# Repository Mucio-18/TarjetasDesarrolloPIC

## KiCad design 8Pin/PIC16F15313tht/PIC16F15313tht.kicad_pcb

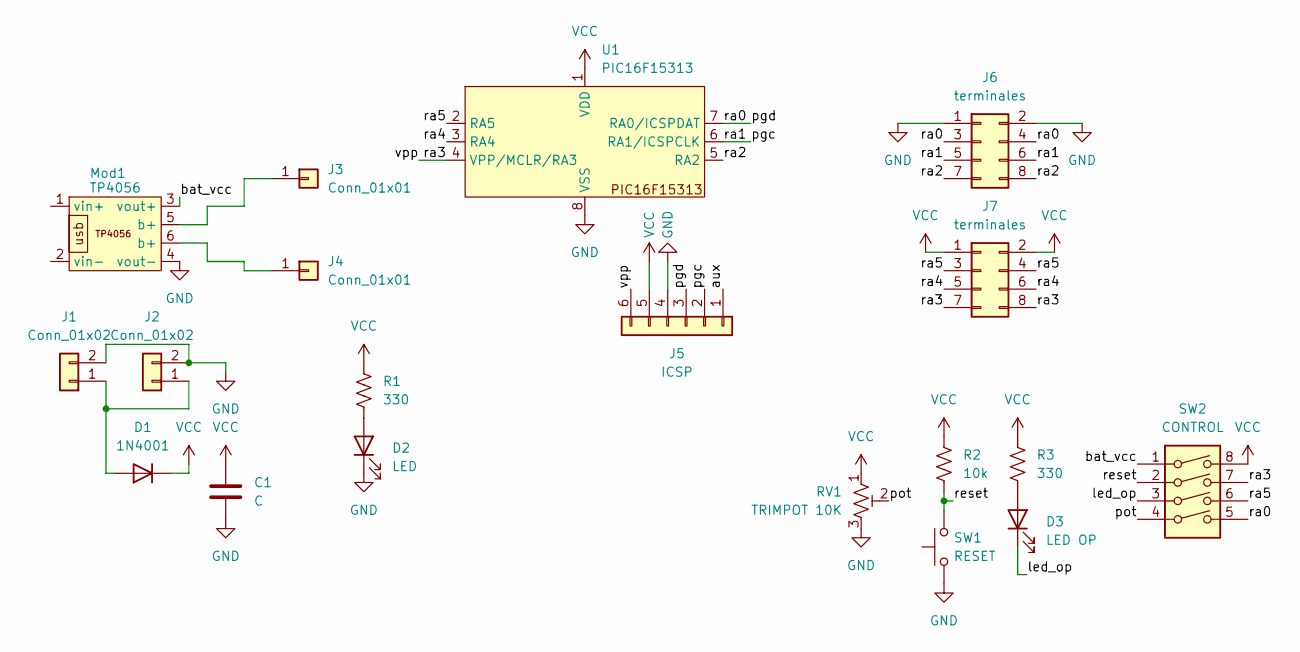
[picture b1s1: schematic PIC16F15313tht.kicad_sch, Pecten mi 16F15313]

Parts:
C1: C; C_Disc_D5.0mm_W2.5mm_P5.00mm
D1: 1N4001; D_DO-41_SOD81_P10.16mm_Horizontal
D2: LED; LED_D3.0mm
D3: LED OP; LED_D3.0mm
J1, J2: Conn_01x02; PinHeader_1x02_P2.54mm_Vertical
J3, J4: Conn_01x01; TestPoint_Pad_D2.5mm
J5: ICSP; PinHeader_1x06_P2.54mm_Horizontal
J6, J7: terminales; PinHeader_2x04_P2.54mm_Vertical
Mod1: TP4056
R1, R3: 330; R_Axial_DIN0207_L6.3mm_D2.5mm_P7.62mm_Horizontal
R2: 10k; R_Axial_DIN0207_L6.3mm_D2.5mm_P7.62mm_Horizontal
RV1: TRIMPOT 10K; Potentiometer_Bourns_3296W_Vertical
SW1: RESET; SW_PUSH_6mm
SW2: CONTROL; SW_DIP_SPSTx04_Slide_6.7x11.72mm_W7.62mm_P2.54mm_LowProfile
U1: PIC16F15313; DIP-8_W7.62mm

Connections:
/aux: J5.1
/bat_vcc: Mod1.3 (vout+), SW2.1
/led_op: D3.1 (K), SW2.3
/pgc: J5.2, J6.5, J6.6, U1.6 (RA1/ICSPCLK)
/pgd: J5.3, J6.3, J6.4, SW2.5, U1.7 (RA0/ICSPDAT)
/pot: RV1.2, SW2.4
/ra2: J6.7, J6.8, U1.5 (RA2)
/ra3: J5.6, J7.7, J7.8, SW2.7, U1.4 (VPP/MCLR/RA3)
/ra4: J7.5, J7.6, U1.3 (RA4)
/ra5: J7.3, J7.4, SW2.6, U1.2 (RA5)
/reset: R2.2, SW1.2, SW2.2
GND: C1.2, D2.1 (K), J1.2, J2.2, J5.4, J6.1, J6.2, Mod1.4 (vout-), RV1.3, SW1.1, U1.8 (VSS)
unnamed: D1.2 (A), J1.1, J2.1
unnamed: D2.2 (A), R1.2
unnamed: D3.2 (A), R3.2
unnamed: J3.1, Mod1.5 (b+)
unnamed: J4.1, Mod1.6 (b+)
VCC: C1.1, D1.1 (K), J5.5, J7.1, J7.2, R1.1, R2.1, R3.1, RV1.1, SW2.8, U1.1 (VDD)

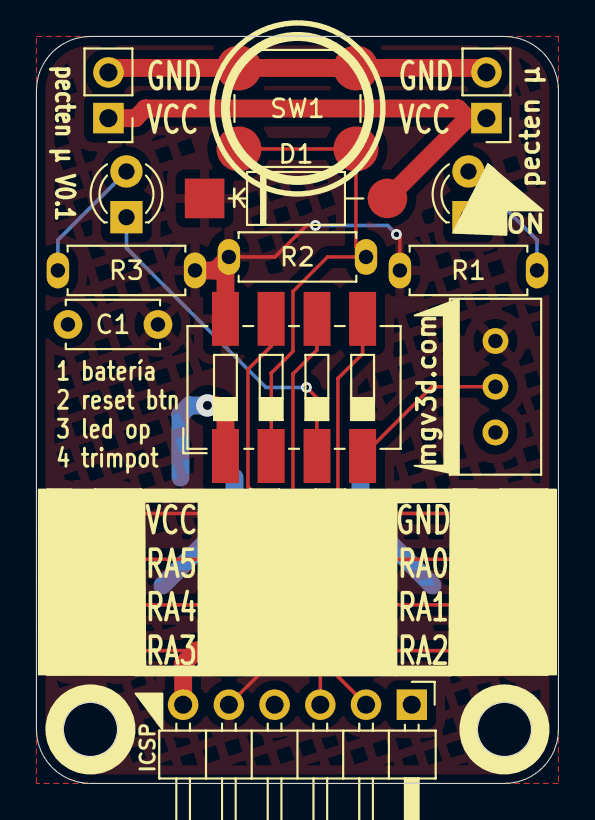
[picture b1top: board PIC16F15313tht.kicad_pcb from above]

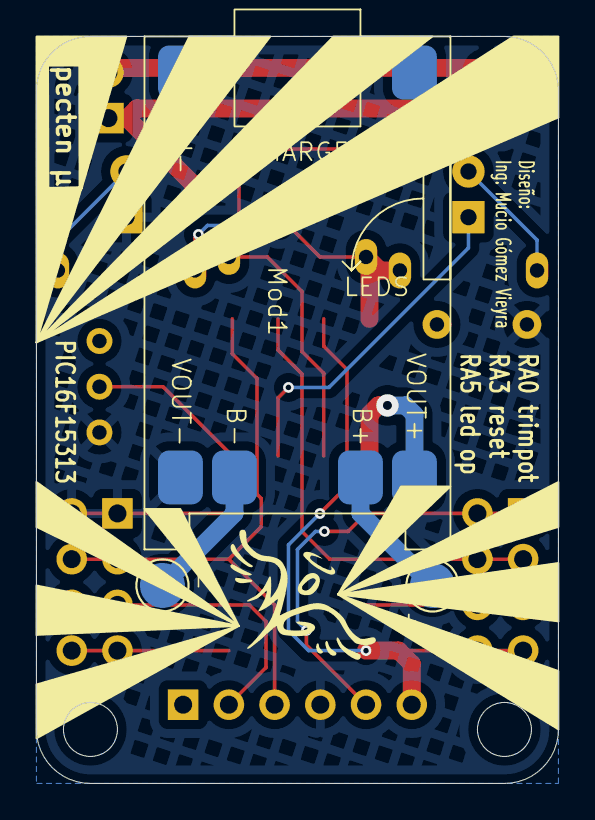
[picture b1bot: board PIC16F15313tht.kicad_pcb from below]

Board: 2 copper layers, 29.0 x 41.5 mm, 20 parts (4 on the bottom side), 17 nets.

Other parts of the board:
G1: LOGO

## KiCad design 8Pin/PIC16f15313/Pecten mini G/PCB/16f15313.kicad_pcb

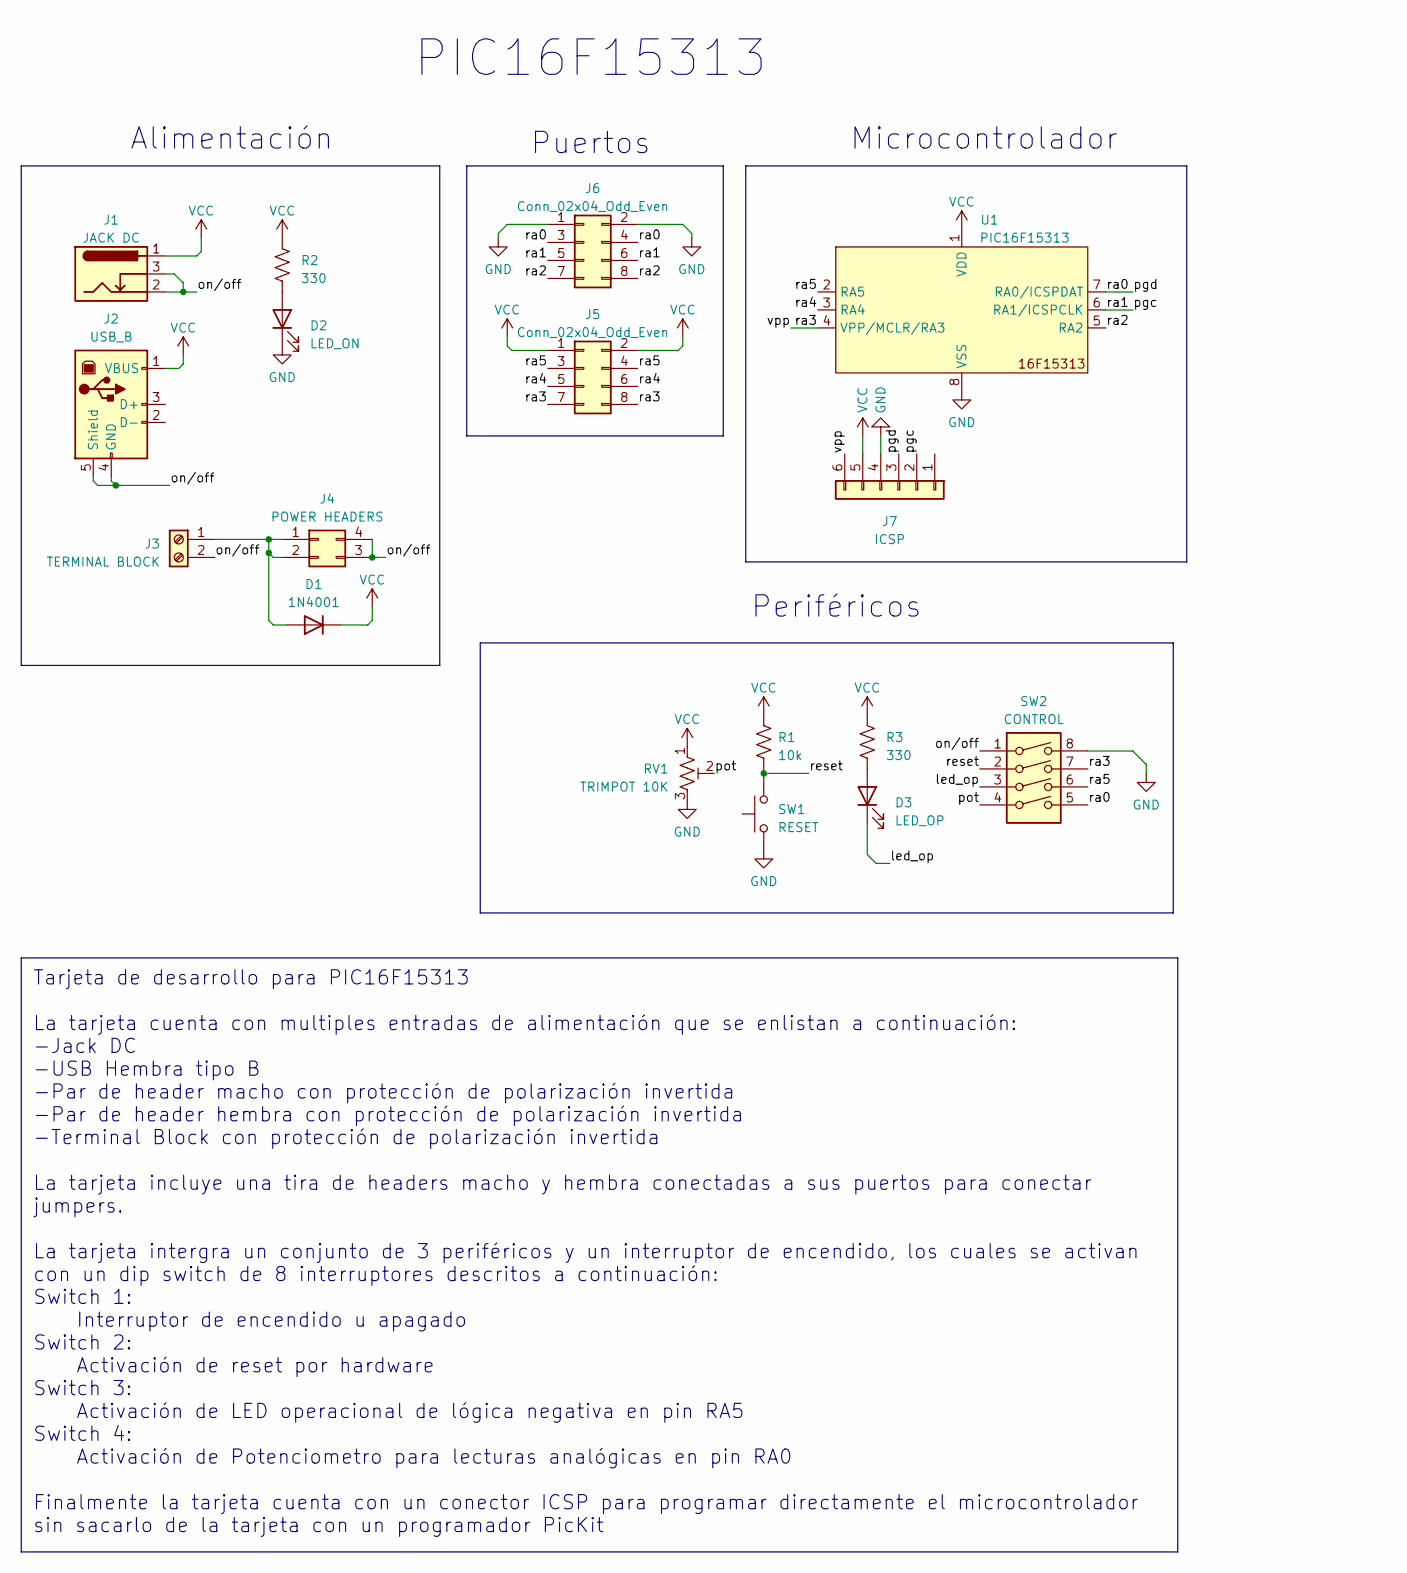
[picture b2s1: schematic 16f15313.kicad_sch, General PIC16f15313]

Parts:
D1: 1N4001; D_DO-41_SOD81_P10.16mm_Horizontal
D2: LED_ON; LED_D3.0mm
D3: LED_OP; LED_D3.0mm
J1: JACK DC; BarrelJack_Kycon_KLDX-0202-xC_Horizontal
J2: USB_B; USB_B_OST_USB-B1HSxx_Horizontal
J3: TERMINAL BLOCK; TerminalBlock_Phoenix_MKDS-1,5-2-5.08_1x02_P5.08mm_Horizont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
J4: POWER HEADERS; PinSocket_2x02_P2.54mm_Vertical
J5, J6: Conn_02x04_Odd_Even; PinSocket_2x04_P2.54mm_Vertical
J7: ICSP; PinHeader_1x06_P2.54mm_Horizontal
R1: 10k; R_Axial_DIN0207_L6.3mm_D2.5mm_P7.62mm_Horizontal
R2, R3: 330; R_Axial_DIN0207_L6.3mm_D2.5mm_P7.62mm_Horizontal
RV1: TRIMPOT 10K; Potentiometer_Vishay_T73YP_Vertical
SW1: RESET; SW_PUSH_6mm_H4.3mm
SW2: CONTROL; SW_DIP_SPSTx04_Slide_6.7x11.72mm_W7.62mm_P2.54mm_LowProfile
U1: PIC16F15313; DIP-8_W7.62mm_Socket_LongPads

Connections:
/led_op: D3.1 (K), SW2.3
/on/off: J1.2, J1.3, J2.4 (GND), J2.5 (Shield), J3.2, J4.3, J4.4, SW2.1
/pgc: J6.5, J6.6, J7.2, U1.6 (RA1/ICSPCLK)
/pgd: J6.3, J6.4, J7.3, SW2.5, U1.7 (RA0/ICSPDAT)
/pot: RV1.2, SW2.4
/ra2: J6.7, J6.8, U1.5 (RA2)
/ra3: J5.7, J5.8, J7.6, SW2.7, U1.4 (VPP/MCLR/RA3)
/ra4: J5.5, J5.6, U1.3 (RA4)
/ra5: J5.3, J5.4, SW2.6, U1.2 (RA5)
/reset: R1.2, SW1.2, SW2.2
GND: D2.1 (K), J6.1, J6.2, J7.4, RV1.3, SW1.1, SW2.8, U1.8 (VSS)
unnamed: D1.2 (A), J3.1, J4.1, J4.2
unnamed: D2.2 (A), R2.2
unnamed: D3.2 (A), R3.2
VCC: D1.1 (K), J1.1, J2.1 (VBUS), J5.1, J5.2, J7.5, R1.1, R2.1, R3.1, RV1.1, U1.1 (VDD)

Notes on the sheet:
Tarjeta de desarrollo para PIC16F15313 La tarjeta cuenta con multiples entradas de alimentación que se enlistan a continuación: -Jack DC -USB Hembra tipo B -Par de header macho con protección de polarización invertida -Par de header hembra con protección de polarización invertida -Terminal Block co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
Puertos
Periféricos
Microcontrolador
PIC16F15313
Alimentación

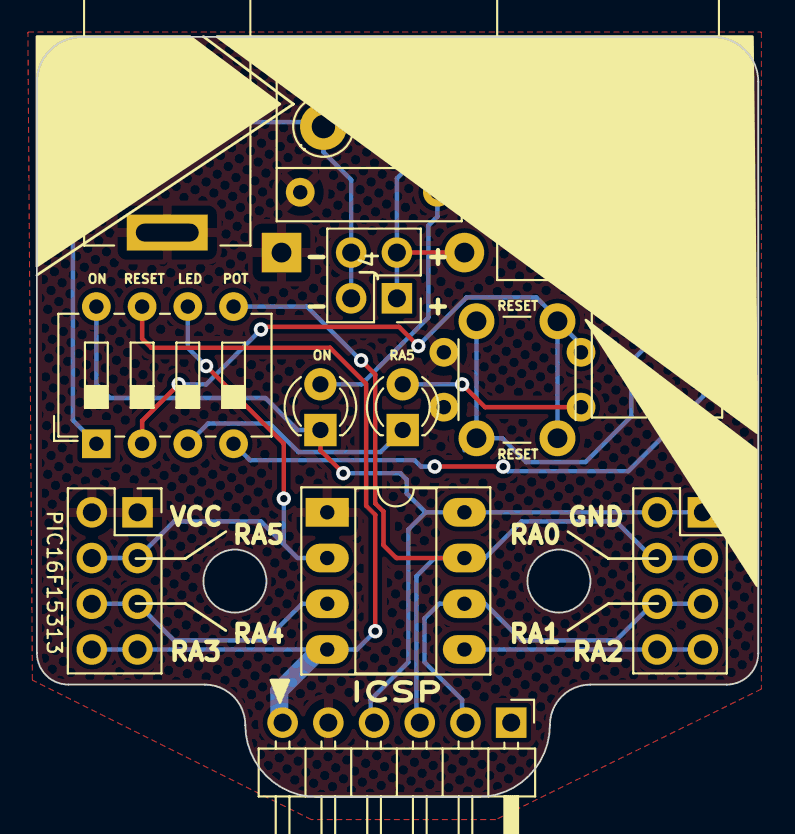
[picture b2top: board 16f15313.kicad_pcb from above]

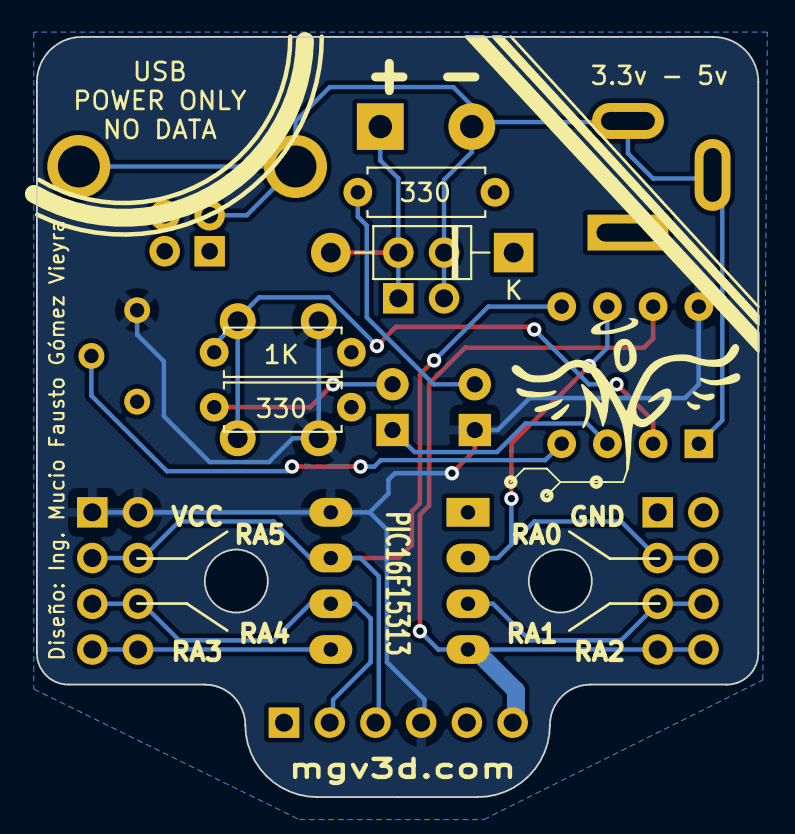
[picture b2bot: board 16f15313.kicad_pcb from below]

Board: 2 copper layers, 40.1 x 42.2 mm, 17 parts (4 on the bottom side), 15 nets.

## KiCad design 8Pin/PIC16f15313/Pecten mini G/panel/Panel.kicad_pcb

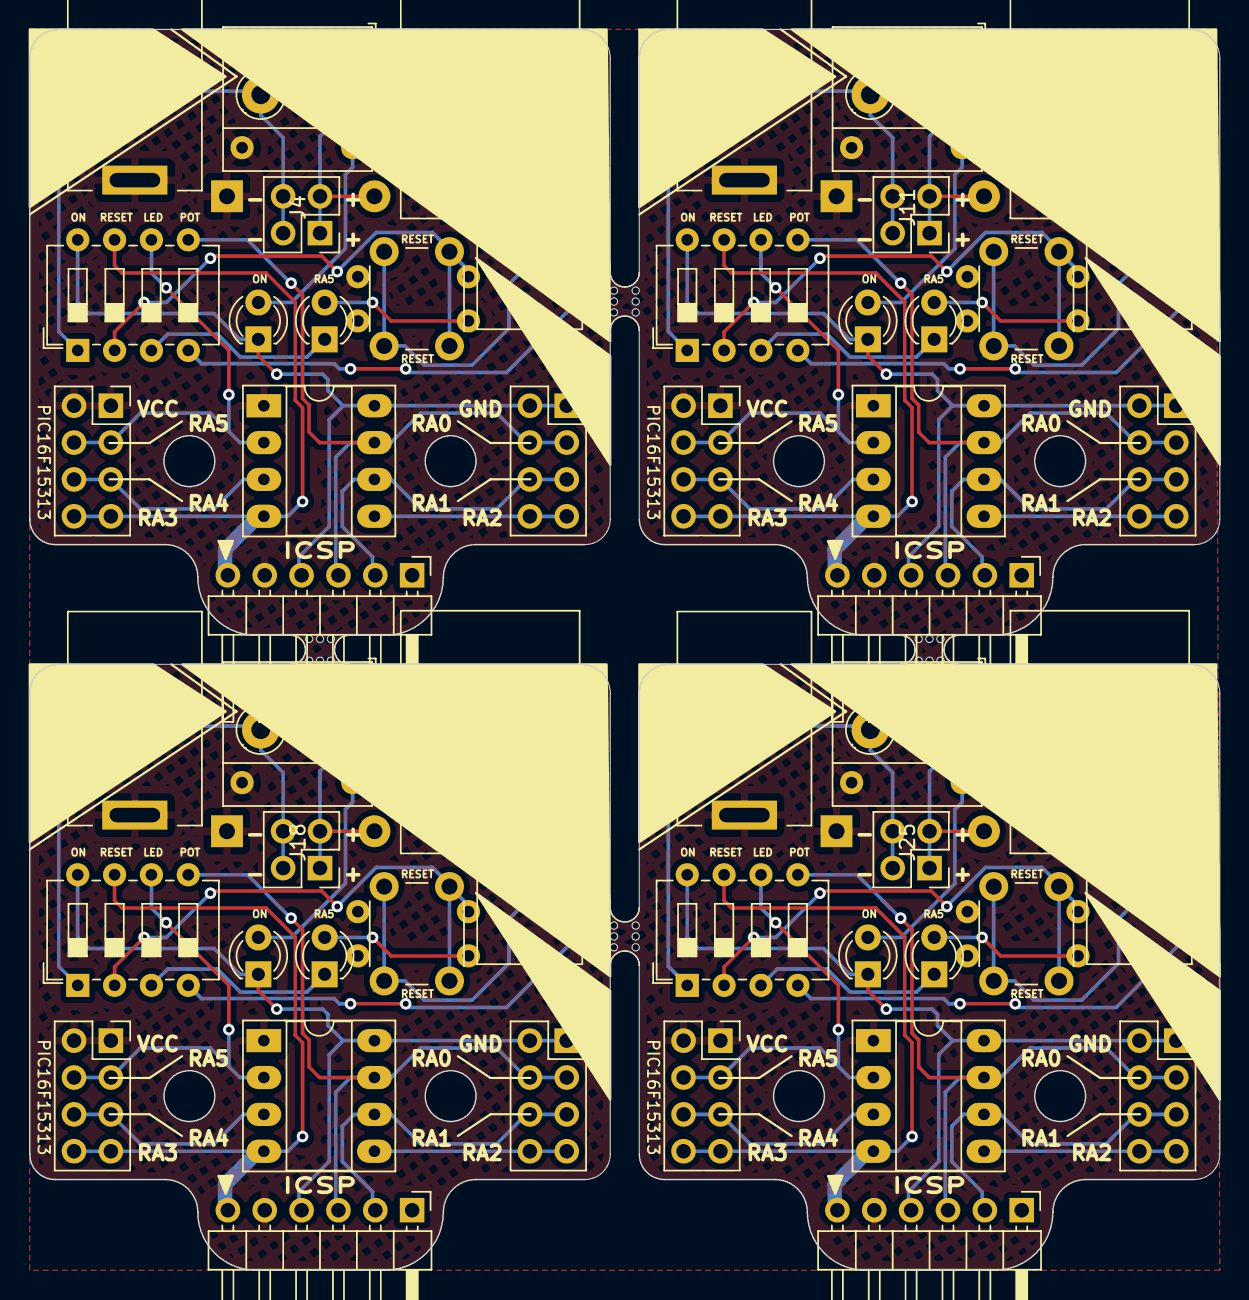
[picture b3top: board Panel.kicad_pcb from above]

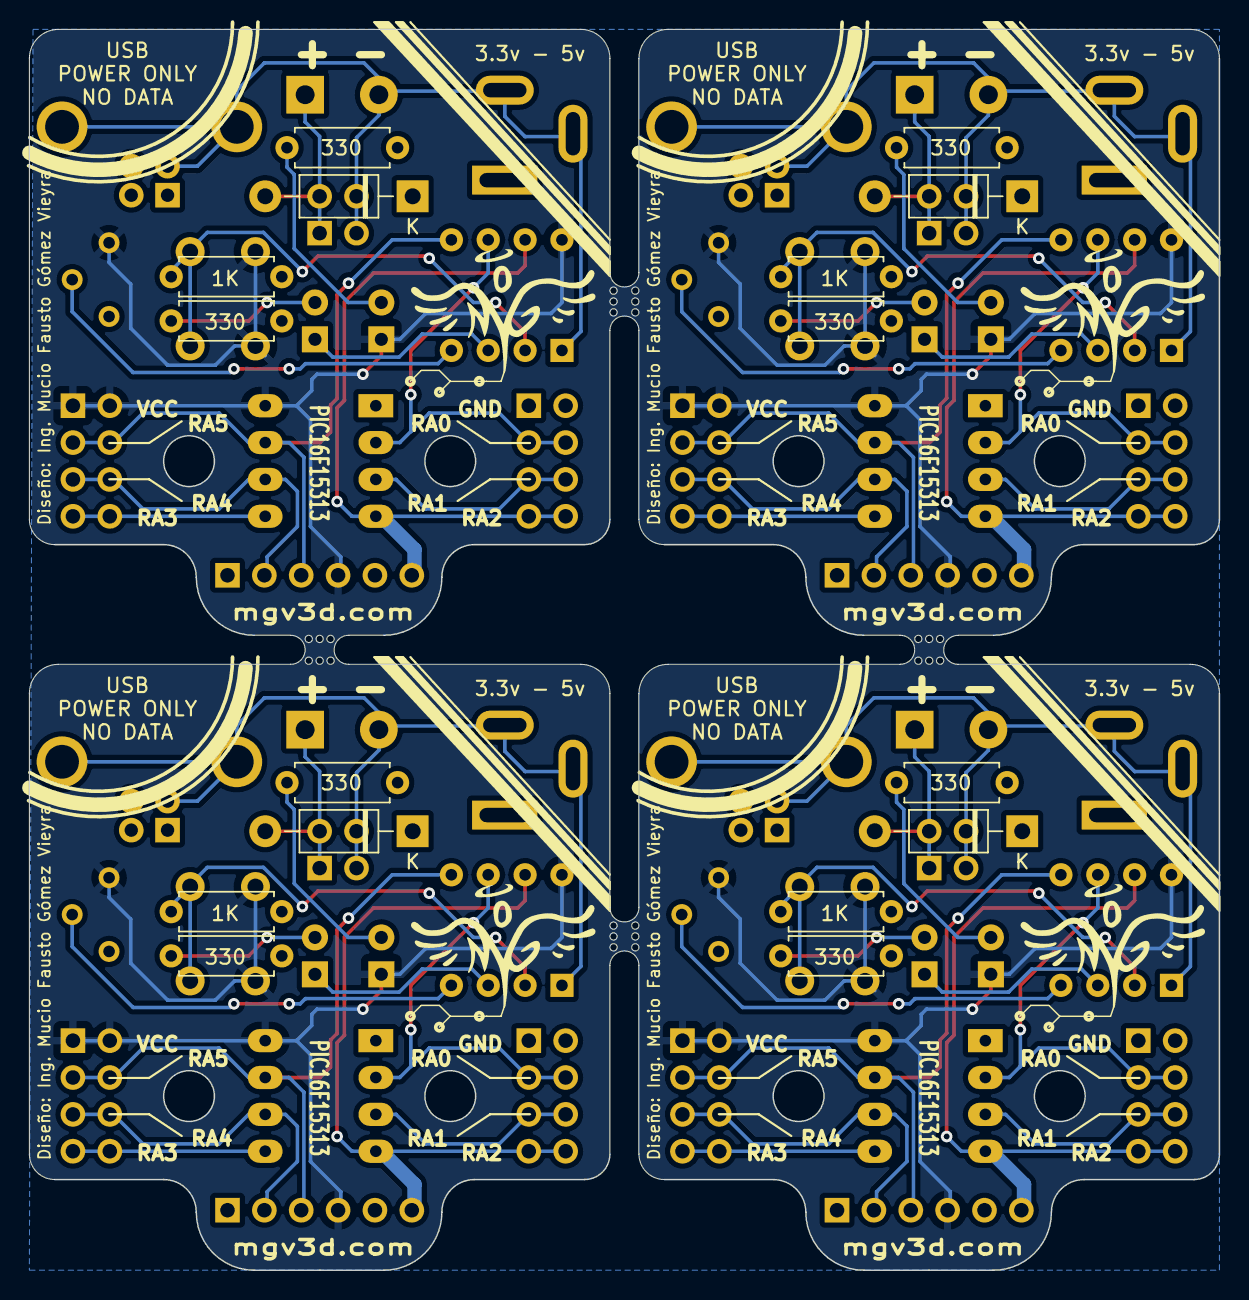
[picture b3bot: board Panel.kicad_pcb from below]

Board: 2 copper layers, 82.0 x 85.5 mm, 72 parts (16 on the bottom side), 15 nets.

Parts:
D1, D4, D7, D10: 1N4001; D_DO-41_SOD81_P10.16mm_Horizontal
D2, D5, D8, D11: LED_ON; LED_D3.0mm
D3, D6, D9, D12: LED_OP; LED_D3.0mm
J1, J8, J15, J22: JACK DC; BarrelJack_Kycon_KLDX-0202-xC_Horizontal
J2, J9, J16, J23: USB_B; USB_B_OST_USB-B1HSxx_Horizontal
J3, J10, J17, J24: TERMINAL BLOCK; TerminalBlock_Phoenix_MKDS-1,5-2-5.08_1x02_P5.08mm_Horizont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
J4, J11, J18, J25: POWER HEADERS; PinSocket_2x02_P2.54mm_Vertical
J5, J6, J12, J13, J19, J20, J26, J27: Conn_02x04_Odd_Even; PinSocket_2x04_P2.54mm_Vertical
J7, J14, J21, J28: ICSP; PinHeader_1x06_P2.54mm_Horizontal
R1, R4, R7, R10: 10k; R_Axial_DIN0207_L6.3mm_D2.5mm_P7.62mm_Horizontal
R2, R3, R5, R6, R8, R9, R11, R12: 330; R_Axial_DIN0207_L6.3mm_D2.5mm_P7.62mm_Horizontal
RV1, RV2, RV3, RV4: TRIMPOT 10K; Potentiometer_Vishay_T73YP_Vertical
SW1, SW3, SW5, SW7: RESET; SW_PUSH_6mm_H4.3mm
SW2, SW4, SW6, SW8: CONTROL; SW_DIP_SPSTx04_Slide_6.7x11.72mm_W7.62mm_P2.54mm_LowProfile
U1, U2, U3, U4: PIC16F15313; DIP-8_W7.62mm_Socket_LongPads
mouse-bite-2mm-slot, mouse-bite-2mm-slot4, mouse-bite-2mm-slot#2, mouse-bite-2mm-slot#3: VAL**; mouse-bite-2mm-slot

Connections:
/led_op: D3.1 (K), D6.1 (K), D9.1 (K), D12.1 (K), SW2.3, SW4.3, SW6.3, SW8.3
/on/off: J1.2, J1.3, J2.4 (GND), J2.5 (Shield), J3.2, J4.3, J4.4, J8.2, J8.3, J9.4 (GND), J9.5 (Shield), J10.2, J11.3, J11.4, J15.2, J15.3, J16.4 (GND), J16.5 (Shield), J17.2, J18.3, J18.4, J22.2, J22.3, J23.4 (GND), J23.5 (Shield), J24.2, J25.3, J25.4, SW2.1, SW4.1, SW6.1, SW8.1
/pgc: J6.5, J6.6, J7.2, J13.5, J13.6, J14.2, J20.5, J20.6, J21.2, J27.5, J27.6, J28.2, U1.6 (RA1/ICSPCLK), U2.6 (RA1/ICSPCLK), U3.6 (RA1/ICSPCLK), U4.6 (RA1/ICSPCLK)
/pgd: J6.3, J6.4, J7.3, J13.3, J13.4, J14.3, J20.3, J20.4, J21.3, J27.3, J27.4, J28.3, SW2.5, SW4.5, SW6.5, SW8.5, U1.7 (RA0/ICSPDAT), U2.7 (RA0/ICSPDAT), U3.7 (RA0/ICSPDAT), U4.7 (RA0/ICSPDAT)
/pot: RV1.2, RV2.2, RV3.2, RV4.2, SW2.4, SW4.4, SW6.4, SW8.4
/ra2: J6.7, J6.8, J13.7, J13.8, J20.7, J20.8, J27.7, J27.8, U1.5 (RA2), U2.5 (RA2), U3.5 (RA2), U4.5 (RA2)
/ra3: J5.7, J5.8, J7.6, J12.7, J12.8, J14.6, J19.7, J19.8, J21.6, J26.7, J26.8, J28.6, SW2.7, SW4.7, SW6.7, SW8.7, U1.4 (VPP/MCLR/RA3), U2.4 (VPP/MCLR/RA3), U3.4 (VPP/MCLR/RA3), U4.4 (VPP/MCLR/RA3)
/ra4: J5.5, J5.6, J12.5, J12.6, J19.5, J19.6, J26.5, J26.6, U1.3 (RA4), U2.3 (RA4), U3.3 (RA4), U4.3 (RA4)
/ra5: J5.3, J5.4, J12.3, J12.4, J19.3, J19.4, J26.3, J26.4, SW2.6, SW4.6, SW6.6, SW8.6, U1.2 (RA5), U2.2 (RA5), U3.2 (RA5), U4.2 (RA5)
/reset: R1.2, R4.2, R7.2, R10.2, SW1.2, SW2.2, SW3.2, SW4.2, SW5.2, SW6.2, SW7.2, SW8.2
GND: D2.1 (K), D5.1 (K), D8.1 (K), D11.1 (K), J6.1, J6.2, J7.4, J13.1, J13.2, J14.4, J20.1, J20.2, J21.4, J27.1, J27.2, J28.4, RV1.3, RV2.3, RV3.3, RV4.3, SW1.1, SW2.8, SW3.1, SW4.8, SW5.1, SW6.8, SW7.1, SW8.8, U1.8 (VSS), U2.8 (VSS), U3.8 (VSS), U4.8 (VSS)
unnamed: D1.2 (A), D4.2 (A), D7.2 (A), D10.2 (A), J3.1, J4.1, J4.2, J10.1, J11.1, J11.2, J17.1, J18.1, J18.2, J24.1, J25.1, J25.2
unnamed: D2.2 (A), D5.2 (A), D8.2 (A), D11.2 (A), R2.2, R5.2, R8.2, R11.2
unnamed: D3.2 (A), D6.2 (A), D9.2 (A), D12.2 (A), R3.2, R6.2, R9.2, R12.2
VCC: D1.1 (K), D4.1 (K), D7.1 (K), D10.1 (K), J1.1, J2.1 (VBUS), J5.1, J5.2, J7.5, J8.1, J9.1 (VBUS), J12.1, J12.2, J14.5, J15.1, J16.1 (VBUS), J19.1, J19.2, J21.5, J22.1, J23.1 (VBUS), J26.1, J26.2, J28.5, R1.1, R2.1, R3.1, R4.1, R5.1, R6.1, R7.1, R8.1, R9.1, R10.1, R11.1, R12.1, RV1.1, RV2.1, RV3.1, RV4.1, U1.1 (VDD), U2.1 (VDD), U3.1 (VDD), U4.1 (VDD)

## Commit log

2024-01-29 Se crearon archivos en esquemático de tarjeta general
2024-02-06 Ruteo de la tarjeta Pecten Mini
2024-02-06 Se finalizó el ruteo y forma de la PCB
2024-02-07 Se terminó la serigrafía de la tarjeta de desarrollo Pecten mini G
2024-02-07 Se agregó archivo de panel PCB
2024-02-08 Se agregaron archivos gerber de la pecten mini g
2025-02-24 avance de actualización del proyecto
2025-02-25 Se inicio la creacion de la huella tp4056
2025-02-26 Se terminó la huella del tp4056
2025-02-26 finalizacion de la tarjeta
2025-02-28 se terminó la tarjeta y se exortaron archivos gerber
